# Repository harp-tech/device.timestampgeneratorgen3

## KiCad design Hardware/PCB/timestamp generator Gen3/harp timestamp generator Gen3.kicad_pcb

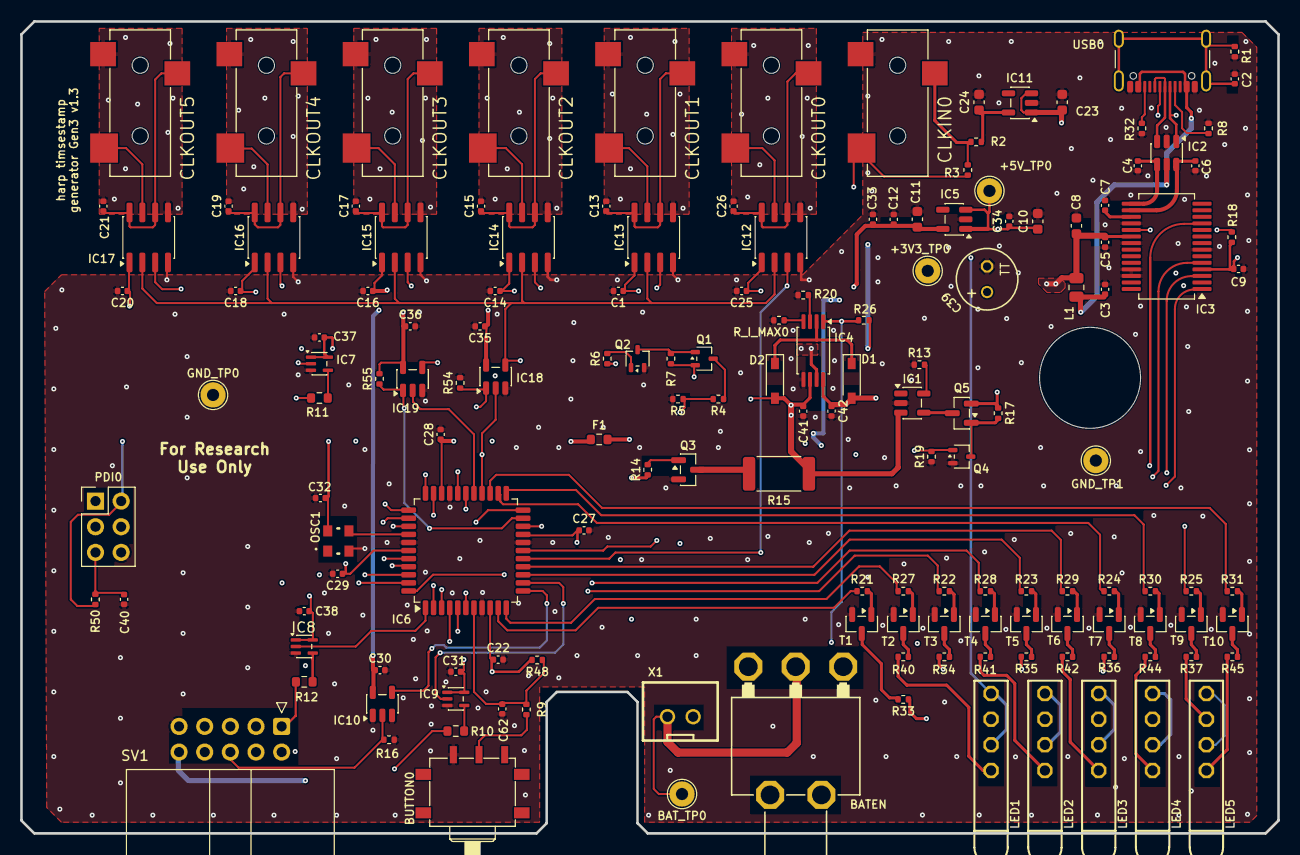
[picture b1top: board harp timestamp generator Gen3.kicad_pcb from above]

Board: 4 copper layers, 124.5 x 80.4 mm, 152 parts (0 on the bottom side), 123 nets.

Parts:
+3V3_TP0, +5V_TP0: TPPAD1-13; TestPoint_THTPad_D2.5mm_Drill1.2mm
BATEN0: 7101MD9ABE; 2M1-SP1-T2-B4-M6RE
BAT_TP0: TPPAD1-13; TestPoint_THTPad_D2.5mm_Drill1.2mm
BUTTON0: CFPA
C1, C3, C5, C7, C9, C12, C13, C14, C15, C16, C17, C18, C19, C20, C21, C22, C25, C26, C27, C28, C30, C31, C32, C35, C36, C37, C38, C41, C42, C62: 100nF; C_0402_1005Metric
C2: 4.7nF; C_0402_1005Metric
C4, C6: 47pF; C_0402_1005Metric
C8, C10, C11, C23, C24: 4.7uF; C_0603_1608Metric
C29: 330nF; C_0402_1005Metric
C33, C34: 10nF; C_0402_1005Metric
C39: 100u; TT2D6_334
C40: 330pF; C_0402_1005Metric
CLKIN0: 35RASMT2BHNTRX
CLKOUT0, CLKOUT1, CLKOUT2, CLKOUT3, CLKOUT4, CLKOUT5: 35RASMT2BHNTRX
D1, D2: DNP; SOD3715X135
F1: BLM18SG331TN1D; R_0603_1608Metric
GND_TP0, GND_TP1: TPPAD1-13; TestPoint_THTPad_D2.5mm_Drill1.2mm
IC1: MCP73831; TSOT-23-5
IC2: USBLC6-2SC6; SOT-23-6
IC3: FT232RL-REEL; SSOP-28_5.3x10.2mm_P0.65mm
IC4: TPS2114; TSSOP-8_4.4x3mm_P0.65mm
IC5, IC11: LP5951MFX-3.3/NOPB; TSOT-23-5
IC6: ATXMEGA16A4U-A; LQFP-44_10x10mm_P0.8mm
IC7, IC8, IC9: M74VHC1GT126DF1G; SOT-353_SC-70-5
IC10, IC18, IC19: SN74LVC1G125DBVT; SOT-23-5
IC12, IC13, IC14, IC15, IC16, IC17: SI8621BC; SOIC-8_3.9x4.9mm_P1.27mm
L1: MI0805K400R-10; R_0805_2012Metric
LED1, LED2, LED3, LED4, LED5: 569-0111-100F; 569-011X-X00_LED_ARRAY
OSC1: O 32,0-JT32C-A-K-3,3-LF; OSCILLATOR_3.2X2.5
PDI0: 67996-206HLF; PinHeader_2x03_P2.54mm_Vertical
Q1: RTU002P02T106; SOT-323_SC-70
Q2: BC817-40W; SOT-323_SC-70
Q3: SBC817; SOT-23
Q4: DMG1012UW; SOT-323_SC-70
Q5: DMP2035U-7; SOT-23
R1: 1M; R_0402_1005Metric
R2: 10R; R_0402_1005Metric
R3, R7, R9, R16, R18, R50, R54, R55: 10k; R_0402_1005Metric
R4: 51k; R_0402_1005Metric
R5, R6: 14.7k; R_0402_1005Metric
R8, R32: 5.1k; R_0402_1005Metric
R10, R11, R12: 100R; R_0603_1608Metric
R13, R17, R19: 4.53k; R_0402_1005Metric
R14, R21, R22, R23, R24, R25, R27, R28, R29, R30, R31: 1k; R_0402_1005Metric
R15: 20R; R_2512_6332Metric
R20: 0R; R_0402_1005Metric
R26: DNP; R_0402_1005Metric
R33, R34, R35, R36, R37, R40, R41, R42, R44, R45: 330R; R_0402_1005Metric
R48: 100k; R_0402_1005Metric
R_I_MAX0: 1k; R_0402_1005Metric
SV1: SBH11-PBPC-D05-RA-BK; IDC-Header_2x05_P2.54mm_Horizontal
T1, T2, T3, T4, T5, T6, T7, T8, T9, T10: BC850; SOT-23
USB0: USB4105-GF-A; USB_C_Receptacle_GCT_USB4105-xx-A_16P_TopMnt_Horizontal
X1: B2B-XH-A(LF)(SN); JST-XH-02-PACKAGE-ROUND-PAD

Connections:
+3V3: +3V3_TP0.1 (1_1), C1.1, C9.1, C11.1, C12.1, C14.1, C16.1, C18.1, C20.1, C25.1, C30.1, C33.1, C35.1, C36.1, F1.2, IC3.4 (VCCIO), IC5.5 (OUT), IC10.5 (VCC), IC12.1 (AVDD), IC13.1 (AVDD), IC14.1 (AVDD), IC15.1 (AVDD), IC16.1 (AVDD), IC17.1 (AVDD), IC18.5 (VCC), IC19.5 (VCC), LED1.A1 (A), LED1.A2 (A), LED2.A1 (A), LED2.A2 (A), LED3.A1 (A), LED3.A2 (A), LED4.A1 (A), LED4.A2 (A), LED5.A1 (A), LED5.A2 (A), R18.1, R55.2
+3V3_u: C22.1, C27.1, C28.1, C29.1, C32.1, F1.1, IC6.9 (VCC@1), IC6.19 (VCC@2), IC6.31 (VCC@3), IC6.39 (AVCC), OSC1.P$4 (VDD), PDI0.2, R48.2, R50.2
+5V: +5V_TP0.1 (1_1), C10.1, C23.1, C31.1, C34.1, C37.1, C38.1, IC4.7 (OUT), IC5.1 (IN), IC5.3 (EN), IC7.1, IC7.5 (VCC), IC8.1, IC8.5 (VCC), IC9.1, IC9.5 (VCC), IC11.1 (IN), IC11.3 (EN), R26.1, SV1.10
+5V_USB: C5.1, C8.1, C39.1, C42.1, D1.2 (A), IC3.20 (VCC), IC4.8 (IN1), L1.1, Q5.2 (S), R17.1
/5VUSB_INPUT: C3.1, IC2.5 (VBUS), L1.2, USB0.A4 (VBUS), USB0.A9 (VBUS), USB0.B4 (VBUS), USB0.B9 (VBUS)
/BAT_READ: IC6.41 (PA1/ADC1), R6.1
/BAT_VOLTAGE: IC6.40 (PA0/ADC0/AREF), R4.2, R5.1
/CHARGE_ENABLE: IC6.5 (PB1/ADC9), Q4.1 (G), R19.1
/DISCHARGE_BAT: IC6.6 (PB2/ADC10/DAC0), R14.1
/FTDI_CTS: IC3.11 (CTS), IC6.29 (~XCK0OC0BSCLPE1)
/FTDI_RTS: IC3.3 (RTS), IC6.28 (~OC0ASDAPE0)
/FTDI_RXD: IC3.5 (RXD), IC6.33 (~TXD0OC0DPE3)
/FTDI_TXD: IC3.1 (TXD), IC6.32 (~RXD0OC0CPE2)
/PWR_GOOD: IC4.1 (STAT), IC6.4 (PB0/ADC8/AREF), R26.2
/Power Management/V_BATT: BATEN0.1 (A), C41.1, D2.2 (A), IC1.3 (VBAT), IC4.6 (IN2), Q1.2 (S), R7.2, R15.1
/USBD+: C4.1, IC2.4 (I/O2), IC3.15 (USBD+)
/USBD-: C6.1, IC2.6 (I/O1), IC3.16 (USBD-)
/core/BLIGHT_EN_UC: IC6.1 (PA5/ADC5), IC8.2
/core/BUTTON: C62.1, IC6.7 (PB3/ADC11/DAC1), R9.2, R48.1
/core/CLOCK_IN: CLKIN0.2, IC6.26 (~RXD1MISOPD6), IC18.2, R3.2
/core/CLOCK_OUT: IC6.27 (~~TXD1SCKCLKOPD7), IC19.2
/core/CLOCK_OUT_ISO: IC7.2, IC12.2 (A1_IN), IC13.2 (A1_IN), IC14.2 (A1_IN), IC15.2 (A1_IN), IC16.2 (A1_IN), IC17.2 (A1_IN), IC18.4, IC19.4
/core/DEVICE_AT_0: IC6.16 (PC6/MISO/RXD1), IC12.3 (A2_OUT)
/core/DEVICE_AT_1: IC6.17 (PC7/SCK/TXD1/CLKO/EVO), IC13.3 (A2_OUT)
/core/DEVICE_AT_2: IC6.44 (PA4/ADC4), IC14.3 (A2_OUT)
/core/DEVICE_AT_3: IC6.36 (PR0/XTAL2), IC15.3 (A2_OUT)
/core/DEVICE_AT_4: IC6.42 (PA2/ADC2), IC16.3 (A2_OUT)
/core/DEVICE_AT_5: IC6.43 (PA3/ADC3), IC17.3 (A2_OUT)
/core/EN_CLOCK_IN: IC6.22 (~OC0CRXD0PD2), IC18.1, R54.1
/core/EN_CLOCK_OUT: IC6.21 (~OC0BXCK0PD1), IC19.1, R55.1
/core/LED_CLK_0: IC6.10 (PC0/OC0A/SDA), R21.1
/core/LED_CLK_1: IC6.3 (PA7/ADC7/AC0-OUT), R22.1
/core/LED_CLK_2: IC6.14 (PC4/OC1A/#SS), R23.1
/core/LED_CLK_3: IC6.11 (PC1/OC0B/XCK0/SCL), R27.2
/core/LED_CLK_4: IC6.2 (PA6/ADC6), R28.1
/core/LED_CLK_5: IC6.15 (PC5/OC1B/MOSI/XCK1), R29.1
/core/LED_LOCK: IC6.24 (~#SSPD4), R24.1
/core/LED_PWR: IC6.20 (~OC0APD0), R25.1
/core/LED_REP: IC6.23 (~OC0DTXD0PD3), R30.1
/core/LEDs & IDC socket/BLIGHT_EN: R12.2, SV1.1
/core/LEDs & IDC socket/IDC_CLOCK_OUT: R11.1, SV1.2
/core/LEDs & IDC socket/RX: IC10.2, R16.1, SV1.6
/core/LEDs & IDC socket/TX: R10.1, SV1.4
/core/PDI-CLK: C40.1, IC6.35 (RESET/PDI-CLK), PDI0.5, R50.1
/core/PDI-DATA: IC6.34 (PDI-DATA), PDI0.1
/core/STATE: IC6.25 (~XCK1MOSIPD5), R31.1
/core/UC_RX: IC6.12 (PC2/OC0C/RXD0), IC10.4
/core/UC_TX: IC6.13 (PC3/OC0D/TXD0), IC9.2
GND: BUTTON0.1 (A), C1.2, C2.2, C3.2, C4.2, C5.2, C6.2, C7.2, C8.2, C9.2, C10.2, C11.2, C12.2, C14.2, C16.2, C18.2, C20.2, C22.2, C23.2, C24.2, C25.2, C27.2, C28.2, C29.2, C30.2, C31.2, C32.2, C33.2, C34.2, C35.2, C36.2, C37.2, C38.2, C39.2, C40.2, C41.2, C42.2, C62.2, CLKIN0.1, GND_TP0.1 (1_1), GND_TP1.1 (1_1), IC1.2 (VSS), IC2.2 (GND), IC3.7 (GND), IC3.18 (GND), IC3.21 (GND), IC3.25 (AGND), IC3.26 (TEST), IC4.5 (GND), IC5.2 (GND), IC6.8 (GND@1), IC6.18 (GND@2), IC6.30 (GND@3), IC6.38 (GND@4), IC7.3 (GND), IC8.3 (GND), IC9.3 (GND), IC10.1, IC10.3 (GND), IC11.2 (GND), IC12.4 (AGND), IC13.4 (AGND), IC14.4 (AGND), IC15.4 (AGND), IC16.4 (AGND), IC17.4 (AGND), IC18.3 (GND), IC19.3 (GND), OSC1.P$2 (GND), PDI0.6, Q2.2 (E), Q3.2 (E), Q4.2 (S), R1.2, R5.2, R8.2, R13.1, R16.2, R19.2, R20.1, R32.2, R54.2, R_I_MAX0.2, SV1.9, T1.2 (E), T2.2 (E), T3.2 (E), T4.2 (E), T5.2 (E), T6.2 (E), T7.2 (E), T8.2 (E), T9.2 (E), T10.2 (E), USB0.A1 (GND), USB0.A12 (GND), USB0.B1 (GND), USB0.B12 (GND), X1.2
unnamed: BATEN0.2 (B), BAT_TP0.1 (1_1), X1.1
unnamed: BUTTON0.2 (B), R9.1
unnamed: CLKIN0.3, R2.2, R3.1
unnamed: D1.1 (K), D2.1 (K), IC4.2 (D0)
unnamed: IC1.5 (PROG), R13.2
unnamed: IC1.4 (VDD), Q5.3 (D)
unnamed: IC2.1 (I/O1), USB0.A7 (D-), USB0.B7 (D-)
unnamed: IC2.3 (I/O2), USB0.A6 (D+), USB0.B6 (D+)
unnamed: C7.1, IC3.17 (3V3OUT)
unnamed: IC3.19 (~RESET), R18.2
unnamed: IC4.3 (D1), R20.2
unnamed: IC4.4 (ILIM), R_I_MAX0.1
unnamed: IC6.37 (PR1/XTAL1), OSC1.P$3 (OUTPUT)
unnamed: IC7.4, R11.2
unnamed: IC8.4, R12.1
unnamed: IC9.4, R10.2
unnamed: C24.1, IC11.5 (OUT), R2.1
unnamed: CLKOUT0.2, IC12.7 (B1_OUT)
unnamed: C26.1, CLKOUT0.3, IC12.6 (B2_IN), IC12.8 (BVDD)
unnamed: C26.2, CLKOUT0.1, IC12.5 (BGND)
unnamed: CLKOUT1.2, IC13.7 (B1_OUT)
unnamed: C13.1, CLKOUT1.3, IC13.6 (B2_IN), IC13.8 (BVDD)
unnamed: C13.2, CLKOUT1.1, IC13.5 (BGND)
unnamed: CLKOUT2.2, IC14.7 (B1_OUT)
unnamed: C15.1, CLKOUT2.3, IC14.6 (B2_IN), IC14.8 (BVDD)
unnamed: C15.2, CLKOUT2.1, IC14.5 (BGND)
unnamed: CLKOUT3.2, IC15.7 (B1_OUT)
unnamed: C17.1, CLKOUT3.3, IC15.6 (B2_IN), IC15.8 (BVDD)
unnamed: C17.2, CLKOUT3.1, IC15.5 (BGND)
unnamed: CLKOUT4.2, IC16.7 (B1_OUT)
unnamed: C19.1, CLKOUT4.3, IC16.6 (B2_IN), IC16.8 (BVDD)
unnamed: C19.2, CLKOUT4.1, IC16.5 (BGND)
unnamed: CLKOUT5.2, IC17.7 (B1_OUT)
unnamed: C21.1, CLKOUT5.3, IC17.6 (B2_IN), IC17.8 (BVDD)
unnamed: C21.2, CLKOUT5.1, IC17.5 (BGND)
unnamed: LED1.C1 (C), R40.1
unnamed: LED1.C2 (C), R33.1
unnamed: LED2.C1 (C), R41.1
unnamed: LED2.C2 (C), R34.1
unnamed: LED3.C1 (C), R42.1
unnamed: LED3.C2 (C), R35.1
unnamed: LED4.C1 (C), R44.1
unnamed: LED4.C2 (C), R36.1
unnamed: LED5.C1 (C), R45.1
unnamed: LED5.C2 (C), R37.1
unnamed: Q1.3 (D), R4.1
unnamed: Q1.1 (G), Q2.3 (C), R7.1
unnamed: Q2.1 (B), R6.2
unnamed: Q3.1 (B), R14.2
unnamed: Q3.3 (C), R15.2
unnamed: Q4.3 (D), Q5.1 (G), R17.2
unnamed: R21.2, T1.1 (B)
unnamed: R33.2, T1.3 (C)
unnamed: R27.1, T2.1 (B)
unnamed: R40.2, T2.3 (C)
unnamed: R22.2, T3.1 (B)
unnamed: R34.2, T3.3 (C)
unnamed: R28.2, T4.1 (B)
unnamed: R41.2, T4.3 (C)
unnamed: R23.2, T5.1 (B)
unnamed: R35.2, T5.3 (C)
unnamed: R29.2, T6.1 (B)
unnamed: R42.2, T6.3 (C)
unnamed: R24.2, T7.1 (B)
unnamed: R36.2, T7.3 (C)
unnamed: R30.2, T8.1 (B)
unnamed: R44.2, T8.3 (C)
unnamed: R25.2, T9.1 (B)
unnamed: R37.2, T9.3 (C)
unnamed: R31.2, T10.1 (B)
unnamed: R45.2, T10.3 (C)
unnamed: R8.1, USB0.A5 (CC1)
unnamed: R32.1, USB0.B5 (CC2)
unnamed: C2.1, R1.1, USB0.SH (SHIELD)

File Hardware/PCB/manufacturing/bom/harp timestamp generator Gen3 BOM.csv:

"#","Qty","Reference","Value","Tolerance","Footprint","TempCo","Voltage","DNP","OEPSPN","MPN"
"1","1","BATEN0","7101MD9ABE","","harp_timestamp_generator_Gen3:2M1-SP1-T2-B4-M6RE","","","","OEPS100019","7101MD9ABE"
"2","1","BUTTON0","CFPA","","harp_timestamp_generator_Gen3:CFPA","","","","OEPS100018","CFPA-1FB4-A2T"
"3","30","C1,C3,C5,C7,C9,C12,C13,C14,C15,C16,C17,C18,C19,C20,C21,C22,C25,C26,C27,C28,C30,C31,C32,C35,C36,C37,C38,C41,C42,C62","100nF","10%","Capacitor_SMD:C_0402_1005Metric","X7R","50V","","OEPS010016","CGA2B3X7R1H104K050BB"
"4","1","C2","4.7nF","10%","Capacitor_SMD:C_0402_1005Metric","X7R","100V","","OEPS010017","885012205084"
"5","2","C4,C6","47pF","5%","Capacitor_SMD:C_0402_1005Metric","C0G","50V","","OEPS010011","04025A470JAT2A"
"6","5","C8,C10,C11,C23,C24","4.7uF","10%","Capacitor_SMD:C_0603_1608Metric","X6S","16V","","OEPS010018","C1608X6S1C475K080AC"
"7","1","C29","330nF","10%","Capacitor_SMD:C_0402_1005Metric","X5R","10V","","OEPS010021","GRM155R61A334KE15D"
"8","2","C33,C34","10nF","10%","Capacitor_SMD:C_0402_1005Metric","X7R","25V","","OEPS010002","GCM155R71E103KA37D"
"9","1","C39","100u","20%","harp_timestamp_generator_Gen3:TT2D6_334","","25V","","OEPS210005","EEU-FM1E101B"
"10","1","C40","330pF","5%","Capacitor_SMD:C_0402_1005Metric","C0G","50V","","OEPS010020","C0402C331J5GAC7867"
"11","7","CLKIN0,CLKOUT0,CLKOUT1,CLKOUT2,CLKOUT3,CLKOUT4,CLKOUT5","35RASMT2BHNTRX","","harp_timestamp_generator_Gen3:35RASMT2BHNTRX","","","","OEPS070025","35RASMT2BHNTRX"
"12","2","D1,D2","DNP","","harp_timestamp_generator_Gen3:SOD3715X135","","","DNP","OEPS000000","DNP"
"13","1","F1","BLM18SG331TN1D","","Resistor_SMD:R_0603_1608Metric","","","","OEPS040004","BLM18SG331TN1D"
"14","1","IC1","MCP73831","","Package_TO_SOT_SMD:TSOT-23-5","","","","OEPS080035","MCP73831T-2ATI/OT"
"15","1","IC2","USBLC6-2SC6","","Package_TO_SOT_SMD:SOT-23-6","","","","OEPS030010","USBLC6-2SC6"
"16","1","IC3","FT232RL-REEL","","Package_SO:SSOP-28_5.3x10.2mm_P0.65mm","","","","OEPS080013","FT232RL-REEL"
"17","1","IC4","TPS2114","","Package_SO:TSSOP-8_4.4x3mm_P0.65mm","","","","OEPS080039","TPS2114APW"
"18","2","IC5,IC11","LP5951MFX-3.3/NOPB","","Package_TO_SOT_SMD:TSOT-23-5","","","","OEPS080026","LP5951MFX-3.3/NOPB"
"19","1","IC6","ATXMEGA16A4U-A","","Package_QFP:LQFP-44_10x10mm_P0.8mm","","","","OEPS080032","ATXMEGA16A4U-A"
"20","3","IC7,IC8,IC9","M74VHC1GT126DF1G","","Package_TO_SOT_SMD:SOT-353_SC-70-5","","","","OEPS080033","M74VHC1GT126DF1G"
"21","3","IC10,IC18,IC19","SN74LVC1G125DBVT","","Package_TO_SOT_SMD:SOT-23-5","","","","OEPS080029","SN74LVC1G125DBVT"
"22","6","IC12,IC13,IC14,IC15,IC16,IC17","SI8621BC","","Package_SO:SOIC-8_3.9x4.9mm_P1.27mm","","","","OEPS080031","SI8621BC-B-ISR"
"23","1","L1","MI0805K400R-10","","Resistor_SMD:R_0805_2012Metric","","","","OEPS040003","MI0805K400R-10"
"24","5","LED1,LED2,LED3,LED4,LED5","569-0111-100F","","harp_timestamp_generator_Gen3:569-011X-X00_LED_ARRAY","","","","OEPS030007","569-0111-100F"
"25","1","OSC1","O 32,0-JT32C-A-K-3,3-LF","","harp_timestamp_generator_Gen3:OSCILLATOR_3.2X2.5","","","","OEPS080014","O 32,0-JT32C-A-K-3,3-LF"
"26","1","PDI0","67996-206HLF","","Connector_PinHeader_2.54mm:PinHeader_2x03_P2.54mm_Vertical","","","","OEPS070015","67996-206HLF"
"27","1","Q1","RTU002P02T106","","Package_TO_SOT_SMD:SOT-323_SC-70","","","","OEPS060009","RTU002P02T106"
"28","1","Q2","BC817-40W","","Package_TO_SOT_SMD:SOT-23","","","","OEPS060007","BC817-40W,135"
"29","1","Q3","SBC817","","Package_TO_SOT_SMD:SOT-23","","","","OEPS060008","SBC817-40LT1G"
"30","1","Q4","DMG1012UW","","Package_TO_SOT_SMD:SOT-323_SC-70","","","","OEPS060010","DMG1012UW-7"
"31","1","Q5","DMP2035U-7","","Package_TO_SOT_SMD:SOT-23","","","","OEPS060011","DMP2035U-7"
"32","1","R1","1M","1%","Resistor_SMD:R_0402_1005Metric","","","","OEPS020026","CRCW04021M00FKED"
"33","1","R2","10R","5%","Resistor_SMD:R_0402_1005Metric","","","","OEPS020041","ERJ-PA2J100X"
"34","8","R3,R7,R9,R16,R18,R50,R54,R55","10k","1%","Resistor_SMD:R_0402_1005Metric","","","","OEPS020030","CRCW040210K0FKED"
"35","1","R4","51k","0.1%","Resistor_SMD:R_0402_1005Metric","","","","OEPS020046","ERA-2AEB513X"
"36","2","R5,R6","14.7k","0.1%","Resistor_SMD:R_0402_1005Metric","","","","OEPS020047","RT0402BRD0714K7L"
"37","2","R8,R32","5.1k","1%","Resistor_SMD:R_0402_1005Metric","","","","OEPS020173","ERJ-2RKF5101X"
"38","3","R10,R11,R12","100R","1%","Resistor_SMD:R_0603_1608Metric","","","","OEPS020042","CRCW0603100RFKEAHP"
"39","3","R13,R17,R19","4.53k","0.1%","Resistor_SMD:R_0402_1005Metric","","","","OEPS020040","RT0402BRD074K53L"
"40","12","R14,R21,R22,R23,R24,R25,R27,R28,R29,R30,R31,R_I_MAX0","1k","1%","Resistor_SMD:R_0402_1005Metric","","","","OEPS020027","CRCW04021K00FKED"
"41","1","R15","20R","1%","Resistor_SMD:R_2512_6332Metric","","","","OEPS020045","CRM2512-FX-20R0ELF"
"42","1","R20","0R","","Resistor_SMD:R_0402_1005Metric","","","","OEPS020001","RC0402JR-070RL"
"43","1","R26","DNP","","Resistor_SMD:R_0402_1005Metric","","","DNP","OEPS000000","DNP"
"44","10","R33,R34,R35,R36,R37,R40,R41,R42,R44,R45","330R","1%","Resistor_SMD:R_0402_1005Metric","","","","OEPS020037","RC0402FR-07330RL"
"45","1","R48","100k","1%","Resistor_SMD:R_0402_1005Metric","","","","OEPS020019","ERJ-2RKF1003X"
"46","1","SV1","SBH11-PBPC-D05-RA-BK","","Connector_IDC:IDC-Header_2x05_P2.54mm_Horizontal","","","","OEPS070027","SBH11-PBPC-D05-RA-BK"
"47","10","T1,T2,T3,T4,T5,T6,T7,T8,T9,T10","BC850","","Package_TO_SOT_SMD:SOT-23","","","","OEPS060006","BC850C,215"
"48","1","USB0","USB4105-GF-A","","Connector_USB:USB_C_Receptacle_GCT_USB4105-xx-A_16P_TopMnt_Horizontal","","","","OEPS070105","USB4105-GF-A"
"49","1","X1","B2B-XH-A(LF)(SN)","","harp_timestamp_generator_Gen3:JST-XH-02-PACKAGE-ROUND-PAD","","","","OEPS070028","B2B-XH-A(LF)(SN)"

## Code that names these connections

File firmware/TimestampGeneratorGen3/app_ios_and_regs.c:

#include <avr/io.h>
#include "hwbp_core_types.h"
#include "app_ios_and_regs.h"

/************************************************************************/
/* Configure and initialize IOs                                         */
/************************************************************************/
void init_ios(void)
{	/* Configure input pins */
	io_pin2in(&PORTA, 2, PULL_IO_TRISTATE, SENSE_IO_NO_INT_USED);        // DEVICE_AT_4
	io_pin2in(&PORTA, 3, PULL_IO_TRISTATE, SENSE_IO_NO_INT_USED);        // DEVICE_AT_5
	io_pin2in(&PORTA, 4, PULL_IO_TRISTATE, SENSE_IO_NO_INT_USED);        // DEVICE_AT_2
	io_pin2in(&PORTB, 0, PULL_IO_UP, SENSE_IO_EDGES_BOTH);               // POWER_GOOD
	io_pin2in(&PORTB, 3, PULL_IO_TRISTATE, SENSE_IO_EDGES_BOTH);         // BUTTON
	io_pin2in(&PORTC, 6, PULL_IO_TRISTATE, SENSE_IO_NO_INT_USED);        // DEVICE_AT_0
	io_pin2in(&PORTC, 7, PULL_IO_TRISTATE, SENSE_IO_NO_INT_USED);        // DEVICE_AT_1
	io_pin2in(&PORTR, 0, PULL_IO_TRISTATE, SENSE_IO_NO_INT_USED);        // DEVICE_AT_3

	/* Configure input interrupts */
	io_set_int(&PORTB, INT_LEVEL_LOW, 0, (1<<0), false);                 // POWER_GOOD

	/* Configure output pins */
	io_pin2out(&PORTA, 1, OUT_IO_DIGITAL, IN_EN_IO_EN);                  // BAT_READ
	io_pin2out(&PORTA, 5, OUT_IO_DIGITAL, IN_EN_IO_EN);                  // EN_SCREEN_BACKLIGHT
	io_pin2out(&PORTA, 6, OUT_IO_DIGITAL, IN_EN_IO_EN);                  // LED_CLK_4
	io_pin2out(&PORTA, 7, OUT_IO_DIGITAL, IN_EN_IO_EN);                  // LED_CLK_1
	io_pin2out(&PORTB, 1, OUT_IO_DIGITAL, IN_EN_IO_EN);                  // EN_CHARGE
	io_pin2out(&PORTB, 2, OUT_IO_DIGITAL, IN_EN_IO_EN);                  // EN_DISCHARGE
	io_pin2out(&PORTC, 0, OUT_IO_DIGITAL, IN_EN_IO_EN);                  // LED_CLK_0
	io_pin2out(&PORTC, 1, OUT_IO_DIGITAL, IN_EN_IO_EN);                  // LED_CLK_3
	io_pin2out(&PORTC, 4, OUT_IO_DIGITAL, IN_EN_IO_EN);                  // LED_CLK_2
	io_pin2out(&PORTC, 5, OUT_IO_DIGITAL, IN_EN_IO_EN);                  // LED_CLK_5
	io_pin2out(&PORTD, 0, OUT_IO_DIGITAL, IN_EN_IO_EN);                  // LED_POWER
	io_pin2out(&PORTD, 1, OUT_IO_DIGITAL, IN_EN_IO_EN);                  // EN_CLOCK_OUT
	io_pin2out(&PORTD, 2, OUT_IO_DIGITAL, IN_EN_IO_EN);                  // EN_CLOCK_IN
	io_pin2out(&PORTD, 3, OUT_IO_DIGITAL, IN_EN_IO_EN);                  // LED_REPEATER
	io_pin2out(&PORTD, 4, OUT_IO_DIGITAL, IN_EN_IO_EN);                  // LED_LOCK
	io_pin2out(&PORTD, 5, OUT_IO_DIGITAL, IN_EN_IO_EN);                  // LED_STATE

	/* Initialize output pins */
	clr_BAT_READ;
	clr_EN_SCREEN_BACKLIGHT;
	clr_LED_CLK_4;
	clr_LED_CLK_1;
	clr_EN_CHARGE;
	clr_EN_DISCHARGE;
	clr_LED_CLK_0;
	clr_LED_CLK_3;
	clr_LED_CLK_2;
	clr_LED_CLK_5;
	clr_LED_POWER;
	clr_EN_CLOCK_OUT;
	set_EN_CLOCK_IN;
	clr_LED_REPEATER;
	clr_LED_LOCK;
	clr_LED_STATE;
}

/************************************************************************/
/* Registers' stuff                                                     */
/************************************************************************/
AppRegs app_regs;

uint8_t app_regs_type[] = {
	TYPE_U8,
	TYPE_U8,
	TYPE_U8,
	TYPE_U8,
	TYPE_FLOAT,
	TYPE_FLOAT,
	TYPE_FLOAT,
	TYPE_U16,
	TYPE_U16,
	TYPE_U32,
	TYPE_U8
};

uint16_t app_regs_n_elements[] = {
	1,
	1,
	1,
	1,
	1,
	1,
	1,
	1,
	1,
	1,
	1
};

uint8_t *app_regs_pointer[] = {
	(uint8_t*)(&app_regs.REG_CONFIG),
	(uint8_t*)(&app_regs.REG_DEVICES_CONNECTED),
	(uint8_t*)(&app_regs.REG_REPEATER_STATUS),
	(uint8_t*)(&app_regs.REG_BATTERY_RATE),
	(uint8_t*)(&app_regs.REG_BATTERY),
	(uint8_t*)(&app_regs.REG_BATTERY_TH_LOW),
	(uint8_t*)(&app_regs.REG_BATTERY_TH_HIGH),
	(uint8_t*)(&app_regs.REG_BATTERY_CALIBRATION0),
	(uint8_t*)(&app_regs.REG_BATTERY_CALIBRATION1),
	(uint8_t*)(&app_regs.REG_TIMER),
	(uint8_t*)(&app_regs.REG_TIMER_FREQUENCY)
};

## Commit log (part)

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2025-07-10 Unpack bit field descriptions for consistent parsing
2026-06-29 Replaced Eagle files with KiCAD.
2026-06-29 Added production files
2026-06-29 Add PCB footprints and 3D models
2026-06-29 Reorganized folders.
2026-06-29 Updated Gerbers.
